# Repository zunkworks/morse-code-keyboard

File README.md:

morse-code-keyboard
===================

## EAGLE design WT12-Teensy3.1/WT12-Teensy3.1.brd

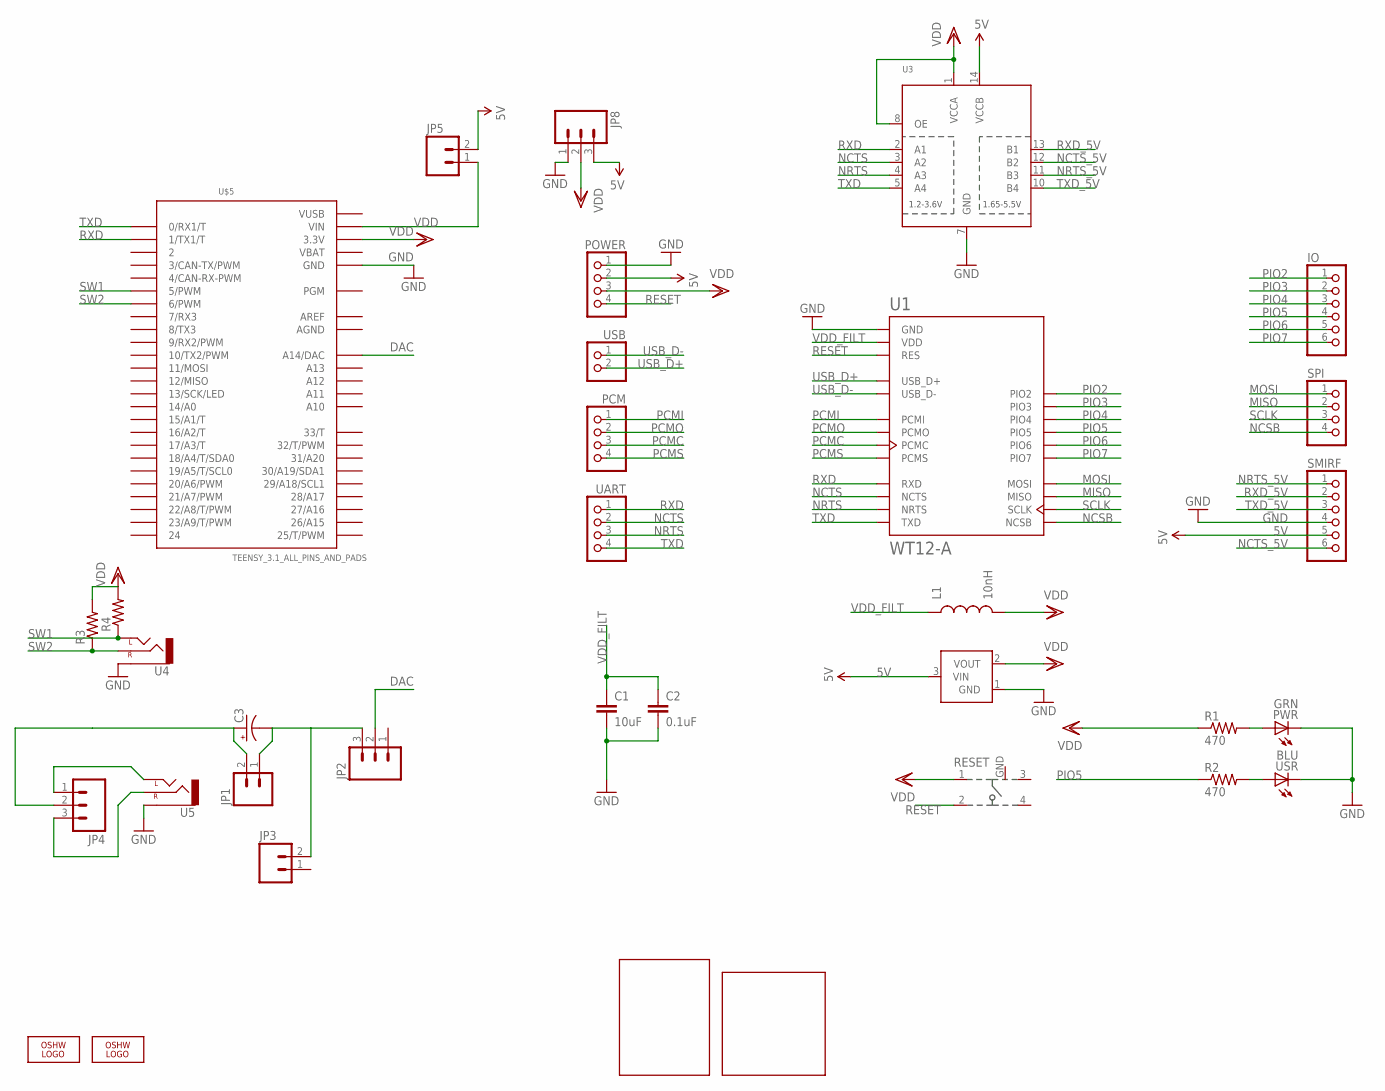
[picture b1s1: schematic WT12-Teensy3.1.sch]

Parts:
C1: 10uF; 0603-CAP
C2: 0.1uF; 0603-CAP
C3: CAP_POLPTH1; CPOL-RADIAL-100UF-25V
IO: PINHD-1X6; 1X06
JP1, JP3, JP5: M02PTH; 1X02
JP2, JP4, JP8: M03PTH; 1X03
L1: 10nH; 0603
LOGO1, LOGO3: OSHW_LOGO_FILLX0070-NT; OSHW_FILLX70_NOTEXT
PCM: PINHD-1X4; 1X04
POWER: PINHD-1X4; 1X04
PWR: GRN; CHIPLED_0805
R1, R2: 470; 0603-RES
R3, R4: RESISTOR0603-RES; 0603-RES
RESET: 101-IG
SMIRF: PINHD-1X6; 1X06
SPI: PINHD-1X4; 1X04
U1: WT12-A
U2: MCP1700; SOT23-3
U3: TXB0104PWR; TSSOP14
U4, U5: AUDIO-JACKPTH; AUDIO-JACK
U$2: PROTOAREA5X6
U$5: TEENSY_3.1_ALL_PINS_AND_PADS; TEENSY_3.1_ALLPINS
U$6: PROTOAREA
UART: PINHD-1X4; 1X04
USB: PINHD-1X2; 1X02
USR: BLU; CHIPLED_0805

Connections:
5V: JP5.2, JP8.3, POWER.2, SMIRF.5, U2.3 (VIN), U3.14 (VCCB)
AGND: U$5.AGND
AREF: U$5.AREF
DAC: JP2.2, U$5.A14 (A14/DAC)
GND: C1.2, C2.2, JP8.1, POWER.1, PWR.C, RESET.GND, SMIRF.4, U1.GND, U1.GND@2 (GND), U1.GND@3 (GND), U1.GND@4 (GND), U2.1 (GND), U3.7 (GND), U4.SLEEVE, U5.SLEEVE, U$5.GND, U$5.GND1 (GND), U$5.GND2 (GND), USR.C
MISO: SPI.2, U1.MISO
MOSI: SPI.1, U1.MOSI
unnamed: PWR.A, R1.2
unnamed: C3.2 (-), JP1.1, JP2.3, JP3.2
unnamed: R2.2, USR.A
unnamed: JP4.1, U5.TIP (LEFT)
unnamed: C3.1 (+), JP1.2, JP4.2
unnamed: JP4.3, U5.RING (RIGHT)
unnamed: JP5.1, U$5.VIN
NCSB: SPI.4, U1.NCSB
NCTS: U1.NCTS, U3.3 (A2), UART.2
NCTS_5V: SMIRF.6, U3.12 (B2)
NRTS: U1.NRTS, U3.4 (A3), UART.3
NRTS_5V: SMIRF.1, U3.11 (B3)
PCMC: PCM.3, U1.PCMC
PCMI: PCM.1, U1.PCMI
PCMO: PCM.2, U1.PCMO
PCMS: PCM.4, U1.PCMS
PIO2: IO.1, U1.PIO2
PIO3: IO.2, U1.PIO3
PIO4: IO.3, U1.PIO4
PIO5: IO.4, R2.1, U1.PIO5
PIO6: IO.5, U1.PIO6
PIO7: IO.6, U1.PIO7
RESET: POWER.4, RESET.2, U1.RES
RXD: U1.RXD, U3.2 (A1), U$5.1 (1/TX1/T), UART.1
RXD_5V: SMIRF.2, U3.13 (B1)
SCLK: SPI.3, U1.SCLK
SW1: R4.1, U4.TIP (LEFT), U$5.5 (5/PWM)
SW2: R3.1, U4.RING (RIGHT), U$5.6 (6/PWM)
TXD: U1.TXD, U3.5 (A4), U$5.0 (0/RX1/T), UART.4
TXD_5V: SMIRF.3, U3.10 (B4)
USB_D+: U1.USB_D+, USB.2
USB_D-: U1.USB_D-, USB.1
VBAT: U$5.VBAT
VDD: JP8.2, L1.2, POWER.3, R1.1, R3.2, R4.2, RESET.1, U2.2 (VOUT), U3.1 (VCCA), U3.8 (OE), U$5.3.3V, U$5.3.3V1 (3.3V), U$5.3.3V2 (3.3V)
VDD_FILT: C1.1, C2.1, L1.1, U1.VDD, U1.VDD@2 (VDD)
VUSB: U$5.VUSB

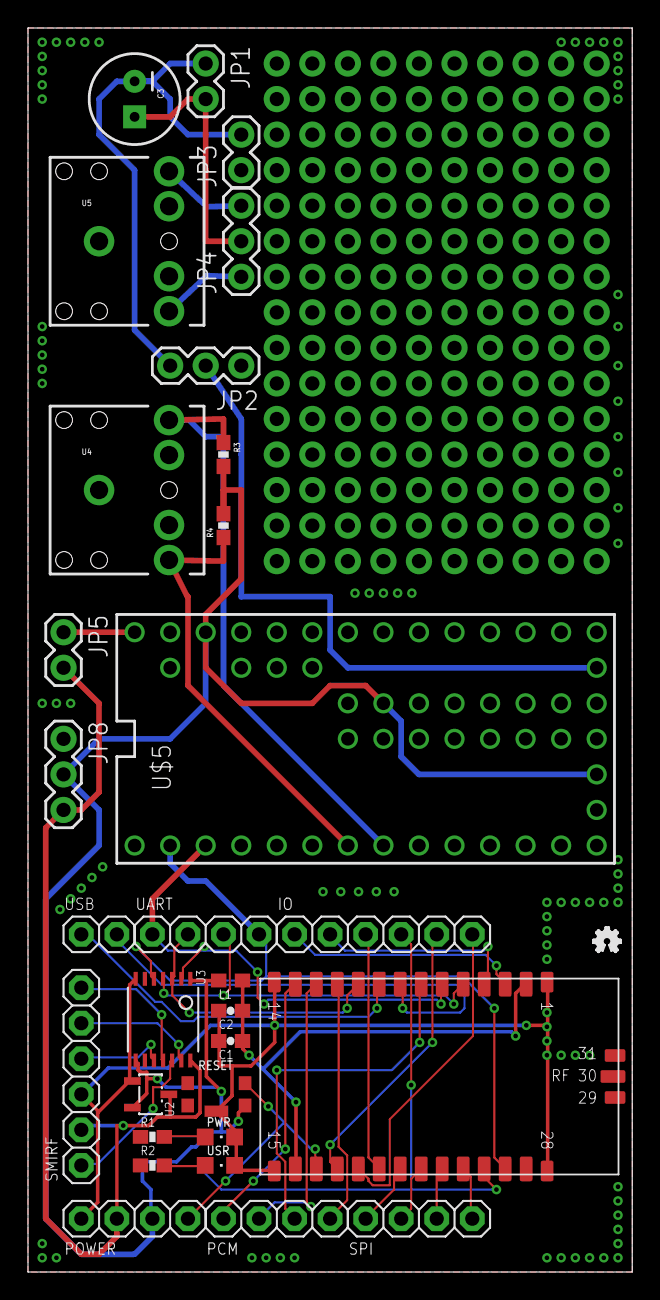
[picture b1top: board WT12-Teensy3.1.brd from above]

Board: 2 copper layers, 43.2 x 88.9 mm, 34 parts (1 on the bottom side), 39 nets.

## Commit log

2014-11-19 Initial commit, it's a mess but everything needed so far is there

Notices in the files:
parts and their libraries:
SparkFun: Licensing: CC v3.0 Share-Alike You are welcome to use this library for commercial purposes.
